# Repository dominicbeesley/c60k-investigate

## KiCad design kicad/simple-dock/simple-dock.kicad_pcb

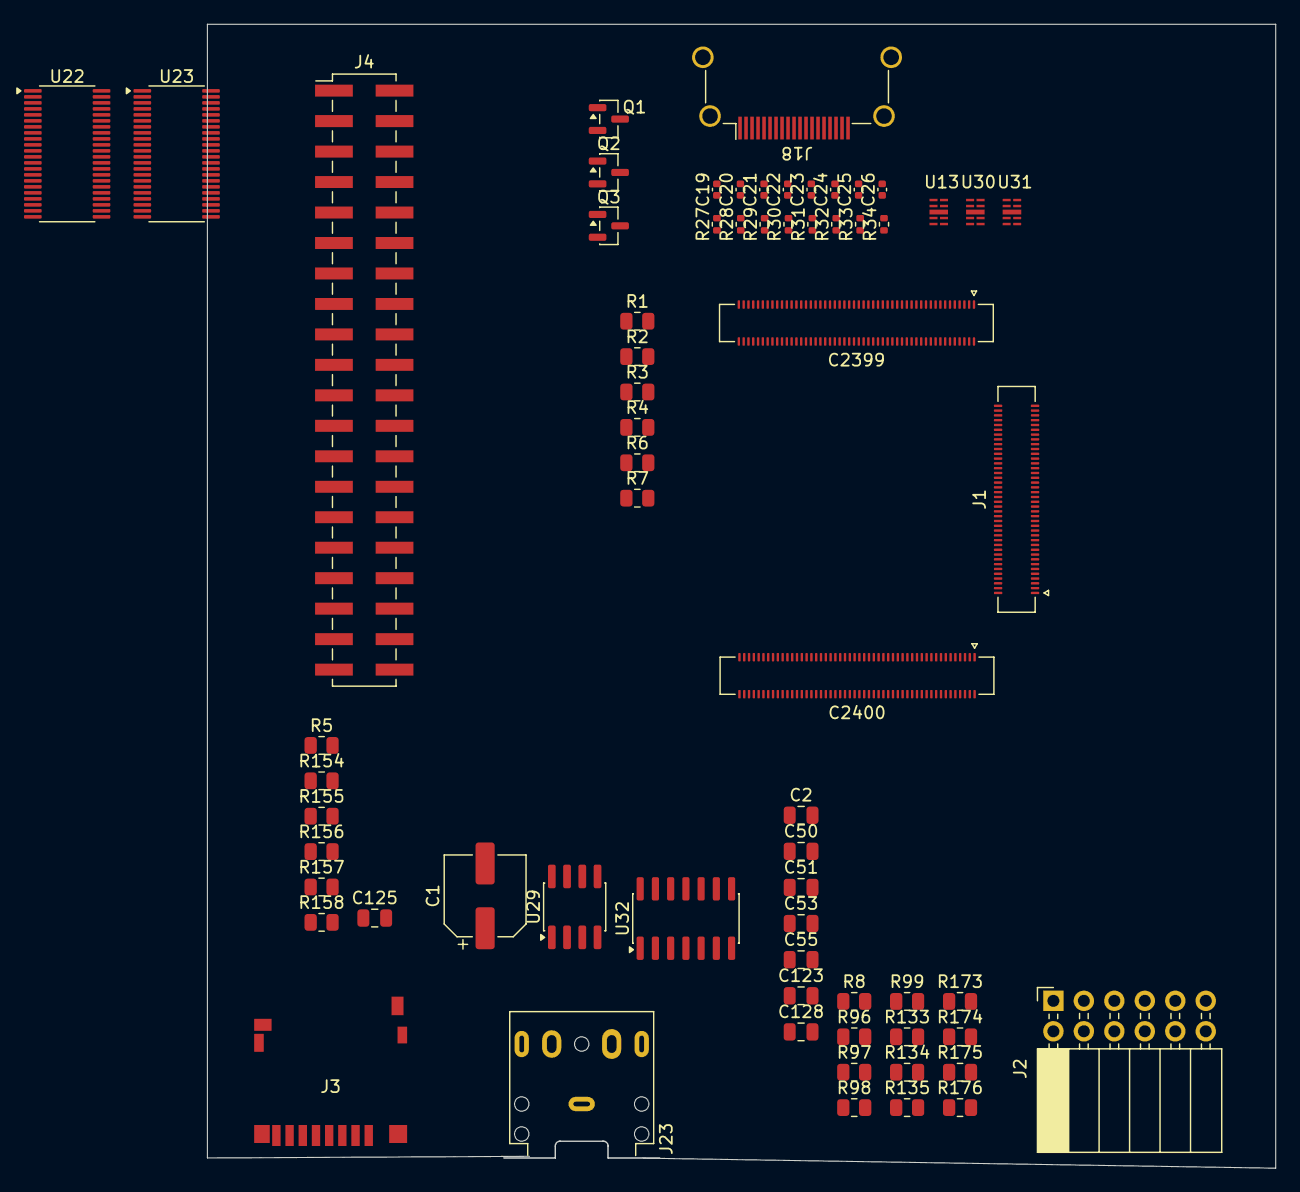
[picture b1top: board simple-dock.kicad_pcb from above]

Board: 2 copper layers, 89.1 x 95.3 mm, 67 parts (0 on the bottom side), 135 nets, no tracks yet.

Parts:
C1: 220u; CP_Elec_6.3x4.5
C2, C125: 100n; C_0805_2012Metric
C19, C20, C21, C22, C23, C24, C25, C26: 100n; C_0402_1005Metric
C50, C53: 3n9; C_0805_2012Metric
C51, C55: 2n2; C_0805_2012Metric
C123, C128: 10u; C_0805_2012Metric
C2399, C2400: Conn_02x50_Odd_Even; Hirose_DF40HC(3.0)-100DS-0.4V_2x50_P0.4mm
J1: Conn_02x40_Odd_Even; Hirose_DF40HC(3.0)-80DS-0.4V_2x40_P0.4mm
J2: Conn_02x06_Odd_Even; PinSocket_2x06_P2.54mm_Horizontal
J3: Micro_SD_Card_Det2; hirose_micro_sd_card_socket
J4: Conn_02x20_Odd_Even; PinHeader_2x20_P2.54mm_Vertical_SMD
J18: HDMI_A; HDMI_A_Amphenol_10029449-x01xLF_Horizontal
J23: line; Jack_3.5mm_CUI_SJ1-3525N_Horizontal_overhang
Q1, Q2, Q3: A03400; SOT-23
R1, R3, R5, R6, R7, R154, R155, R156, R157, R158: 47k; R_0805_2012Metric
R2, R4, R96, R97, R98, R99: 4k7; R_0805_2012Metric
R8, R133, R134, R135: 22; R_0805_2012Metric
R27, R28, R29, R30, R31, R32, R33, R34: 510; R_0402_1005Metric
R173, R174: 220; R_0805_2012Metric
R175, R176: 10k; R_0805_2012Metric
U13, U30, U31: rclamp0524P
U22: generic_2048x8_TSOP_II_44_BB; TSSOP-44_4.4x11mm_P0.5mm
U23: generic_2048x8_TSOP_II_44; TSSOP-44_4.4x11mm_P0.5mm
U29: PT8211; SOP-8_3.76x4.96mm_P1.27mm
U32: LM324A; SO-14_3.9x8.65mm_P1.27mm

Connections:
+3.3VA: C2.1, R8.1, U32.11 (V-)
+3V3: C125.1, J3.4 (VDD), Q1.1 (G), Q2.1 (G), R2.2, R4.2, R5.1, R154.1, R155.1, R156.1, R157.1, R158.1, U23.11 (VDD), U23.33 (VDD)
+5V: C2400.89 (Pin_79), C2400.91 (Pin_79), C2400.93 (Pin_79), C2400.95 (Pin_79), C2400.97 (Pin_79), C2400.99 (Pin_79), J4.11
+5VHDMI: J18.18 (+5V), R3.1, R6.1
/SOM_FPGA/A0: C2399.10, J4.37
/SOM_FPGA/A1: C2399.12, J4.38
/SOM_FPGA/A2: C2399.16, J4.39
/SOM_FPGA/A3: C2399.18, J4.40
/SOM_FPGA/A4: C2399.30, J4.28
/SOM_FPGA/A5: C2399.34, J4.25
/SOM_FPGA/A6: C2399.36, J4.26
/SOM_FPGA/A7: C2399.17, J4.23
/SOM_FPGA/A8: C2399.19, J4.24
/SOM_FPGA/A9: C2399.29, J4.21
/SOM_FPGA/A10: C2399.6, J4.36
/SOM_FPGA/A11: C2399.31, J4.22
/SOM_FPGA/A12: C2399.23, J4.19
/SOM_FPGA/BA0: C2399.40, J4.34
/SOM_FPGA/BA1: C2399.4, J4.35
/SOM_FPGA/BCK: C2400.26, R133.1
/SOM_FPGA/CLK: C2399.25, J4.20
/SOM_FPGA/D0: C2399.65, J4.1
/SOM_FPGA/D1: C2399.67, J4.2
/SOM_FPGA/D2: C2399.59, J4.3
/SOM_FPGA/D3: C2399.61, J4.4
/SOM_FPGA/D4: C2399.53, J4.5
/SOM_FPGA/D5: C2399.55, J4.6
/SOM_FPGA/D6: C2399.47, J4.7
/SOM_FPGA/D7: C2399.49, J4.8
/SOM_FPGA/D8: C2399.7, J4.18
/SOM_FPGA/D9: C2399.5, J4.17
/SOM_FPGA/D10: C2399.13, J4.16
/SOM_FPGA/D11: C2399.11, J4.15
/SOM_FPGA/D12: C2399.37, J4.14
/SOM_FPGA/D13: C2399.35, J4.13
/SOM_FPGA/D14: C2399.43, J4.10
/SOM_FPGA/D15: C2399.41, J4.9
/SOM_FPGA/DAT: C2400.30, R134.1
/SOM_FPGA/DBUG.RX: C2400.54, J2.8
/SOM_FPGA/DBUG.TX: C2400.50, J2.6
/SOM_FPGA/DVI_CK.N: C26.1, C2399.62
/SOM_FPGA/DVI_CK.P: C25.1, C2399.64
/SOM_FPGA/DVI_D0.N: C24.1, C2399.58
/SOM_FPGA/DVI_D0.P: C23.1, C2399.60
/SOM_FPGA/DVI_D1.N: C22.1, C2399.54
/SOM_FPGA/DVI_D1.P: C21.1, C2399.56
/SOM_FPGA/DVI_D2.N: C20.1, C2399.50
/SOM_FPGA/DVI_D2.P: C19.1, C2399.52
/SOM_FPGA/DVI_HPD: C2400.63, R1.1
/SOM_FPGA/DVI_PWR: C2400.61, Q3.1 (G), R7.1
/SOM_FPGA/EDID_SCL: C2400.32, Q1.2 (S), R2.1
/SOM_FPGA/EDID_SDA: C2400.34, Q2.2 (S), R4.1
/SOM_FPGA/JTAG.TCK: J1.7, J2.5
/SOM_FPGA/JTAG.TDI: J1.9, J2.7
/SOM_FPGA/JTAG.TDO: J1.5, J2.9
/SOM_FPGA/JTAG.TMS: J1.3, J2.11
/SOM_FPGA/LDM: C2399.42, J4.29
/SOM_FPGA/Q0_LN1_TX.N: C2399.77, C2399.95 (Pin_79)
/SOM_FPGA/Q0_LN1_TX.P: C2399.79, C2399.97 (Pin_79)
/SOM_FPGA/SDIO.CLK: C2400.46, J3.5 (CLK), R157.2
/SOM_FPGA/SDIO.CMD: C2400.42, J3.3 (CMD), R155.2
/SOM_FPGA/SDIO.D0: C2400.38, J3.7 (DAT0), R154.2
/SOM_FPGA/SDIO.D1: C2400.40, J3.8 (DAT1)
/SOM_FPGA/SDIO.D2: C2400.48, J3.1 (DAT2), R158.2
/SOM_FPGA/SDIO.D3: C2400.44, J3.2 (DAT3/CD), R156.2
/SOM_FPGA/SDIO.DET: C2400.56, J3.10 (DET_A), R5.2
/SOM_FPGA/UDM: C2399.44, J4.30
/SOM_FPGA/WS: C2400.28, R135.1
/SOM_FPGA/~CAS: C2399.22, J4.31
/SOM_FPGA/~CS: J1.72, J4.33
/SOM_FPGA/~RAS: C2399.24, J4.32
/SOM_FPGA/~WE: C2399.28, J4.27
/hdmi/edid_scl_x: J18.15 (SCL), Q1.3 (D), R3.2, U31.2 (I/O2)
/hdmi/edid_sda_x: J18.16 (SDA), Q2.3 (D), R6.2, U31.4 (I/O3)
/hdmi/hdmi_cec_x: J18.13 (CEC), U31.1 (I/O1)
/hdmi/hdmi_hpd_x: J18.19 (HPD), R1.2, U31.5 (I/O4)
/hdmi/tmds_ck_x_N: C26.2, J18.12 (CK-), R34.2, U30.5 (I/O4)
/hdmi/tmds_ck_x_P: C25.2, J18.10 (CK+), R27.2, U30.4 (I/O3)
/hdmi/tmds_d0_x_N: C24.2, J18.9 (D0-), R28.2, U30.2 (I/O2)
/hdmi/tmds_d0_x_P: C23.2, J18.7 (D0+), R29.2, U30.1 (I/O1)
/hdmi/tmds_d1_x_N: C22.2, J18.6 (D1-), R30.2, U13.5 (I/O4)
/hdmi/tmds_d1_x_P: C21.2, J18.4 (D1+), R31.2, U13.4 (I/O3)
/hdmi/tmds_d2_x_N: C20.2, J18.3 (D2-), R32.2, U13.2 (I/O2)
/hdmi/tmds_d2_x_P: C19.2, J18.1 (D2+), R33.2, U13.1 (I/O1)
/sdram/MEM_A0: U22.21 (A16), U23.19 (A8)
/sdram/MEM_A1: U22.20 (A17), U23.18 (A7)
/sdram/MEM_A2: U22.19 (A18), U23.17 (A6)
/sdram/MEM_A3: U22.18 (A19), U23.16 (A5)
/sdram/MEM_A4: U22.24 (A13), U23.26 (A10)
/sdram/MEM_A5: U22.25 (A12), U23.27 (A11)
/sdram/MEM_A6: U22.26 (A11), U23.28 (A12)
/sdram/MEM_A7: U22.27 (A10), U23.29 (A13)
/sdram/MEM_A8: U22.3 (A2), U23.5 (A2)
/sdram/MEM_A9: U22.4 (A1), U23.6 (A3)
/sdram/MEM_A10: U22.22 (A15), U23.20 (A9)
/sdram/MEM_A11: U22.5 (A0), U23.7 (A4)
/sdram/MEM_A12: U22.28 (A9), U23.30 (A14)
/sdram/MEM_A13: U22.2 (A3), U23.4 (A1)
/sdram/MEM_A14: U22.1 (A4), U23.3 (A0)
/sdram/MEM_A15: U22.42 (A7), U23.39 (A16)
/sdram/MEM_A16: U22.43 (A6), U23.40 (A17)
/sdram/MEM_A17: U22.39 (A8), U23.38 (A15)
/sdram/MEM_A18: U22.44 (A5), U23.41 (A18)
/sdram/MEM_A19: U22.23 (A14), U23.25 (A19)
/sdram/MEM_D0: U22.31 (I/O4), U23.31 (I/O4)
/sdram/MEM_D1: U22.32 (I/O5), U23.32 (I/O5)
/sdram/MEM_D2: U22.13 (I/O2), U23.13 (I/O2)
/sdram/MEM_D3: U22.9 (I/O0), U23.9 (I/O0)
/sdram/MEM_D4: U22.36 (I/O7), U23.36 (I/O7)
/sdram/MEM_D5: U22.10 (I/O1), U23.10 (I/O1)
/sdram/MEM_D6: U22.35 (I/O6), U23.35 (I/O6)
/sdram/MEM_D7: U22.14 (I/O3), U23.14 (I/O3)
/sdram/MEM_nOE: U22.41 (~OE), U23.37 (~OE)
/sdram/MEM_nWE: U22.17 (~WE), U23.15 (~WE)
/sdram/RAM0PWR: U22.11 (VDD), U22.33 (VDD), U22.40 (CE2)
GND: C1.2, C2.2, C51.2, C55.2, C125.2, C2399.2, C2399.3, C2399.8, C2399.9, C2399.14, C2399.15, C2399.20, C2399.21, C2399.26, C2399.27, C2399.32, C2399.33, C2399.38, C2399.39, C2399.45, C2399.46, C2399.51, C2399.57, C2399.63, C2399.69, C2399.70, C2399.75, C2399.76, C2399.81 (Pin_79), C2399.82 (Pin_80), C2399.87 (Pin_79), C2399.88 (Pin_80), C2399.93 (Pin_79), C2399.94 (Pin_80), C2399.99 (Pin_79), C2399.100 (Pin_80), C2400.47, C2400.53, C2400.59, C2400.65, C2400.77, C2400.79, C2400.81 (Pin_79), C2400.83 (Pin_79), C2400.85 (Pin_79), C2400.87 (Pin_79), C2400.100 (Pin_80), J1.1, J1.2, J1.8, J1.11, J1.16, J1.17, J1.21, J1.22, J1.27, J1.35, J1.38, J1.60, J1.63, J1.66, J1.79, J2.1, J2.2, J3.6 (VSS), J3.9 (DET_B), J3.11 (SHIELD), J4.12, J18.2 (D2S), J18.5 (D1S), J18.8 (D0S), J18.11 (CKS), J18.17 (GND), J18.SH, J23.S, Q3.2 (S), R7.2, R175.1, R176.1, U13.3 (GND), U22.12 (GND), U22.34 (GND), U23.12 (GND), U23.34 (GND), U29.4 (GND), U30.3 (GND), U31.3 (GND), U32.4 (V+)
unnamed: C50.2, R96.1, R97.2
unnamed: C53.2, R98.2, R99.1
unnamed: C123.1, R173.2
unnamed: C123.2, J23.R, R175.2
unnamed: C128.1, J23.T, R176.2
unnamed: C128.2, R174.2
unnamed: Q3.3 (D), R27.1, R28.1, R29.1, R30.1, R31.1, R32.1, R33.1, R34.1
unnamed: R133.2, U29.1 (BCK)
unnamed: R134.2, U29.3 (DIN)
unnamed: R98.1, U29.6 (LCH)
unnamed: R97.1, U29.8 (RCH)
unnamed: C1.1, R8.2, U29.5 (VDD)
unnamed: R135.2, U29.2 (WS)
unnamed: C55.1, R99.2, U32.3 (+)
unnamed: C53.1, U32.1, U32.2 (-), U32.10 (+)
unnamed: C51.1, R96.2, U32.5 (+)
unnamed: C50.1, U32.6 (-), U32.7, U32.12 (+)
unnamed: R174.1, U32.8, U32.9 (-)
unnamed: R173.1, U32.13 (-), U32.14

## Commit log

2026-05-18 initial checkin
2026-05-18 probed pins confirmed
2026-05-18 Start kicad project
2026-05-19 more kicad
2026-05-20 kicad add usb
